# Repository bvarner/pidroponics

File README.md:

# pidroponics
RaspberryPi Controlled Hydroponics!

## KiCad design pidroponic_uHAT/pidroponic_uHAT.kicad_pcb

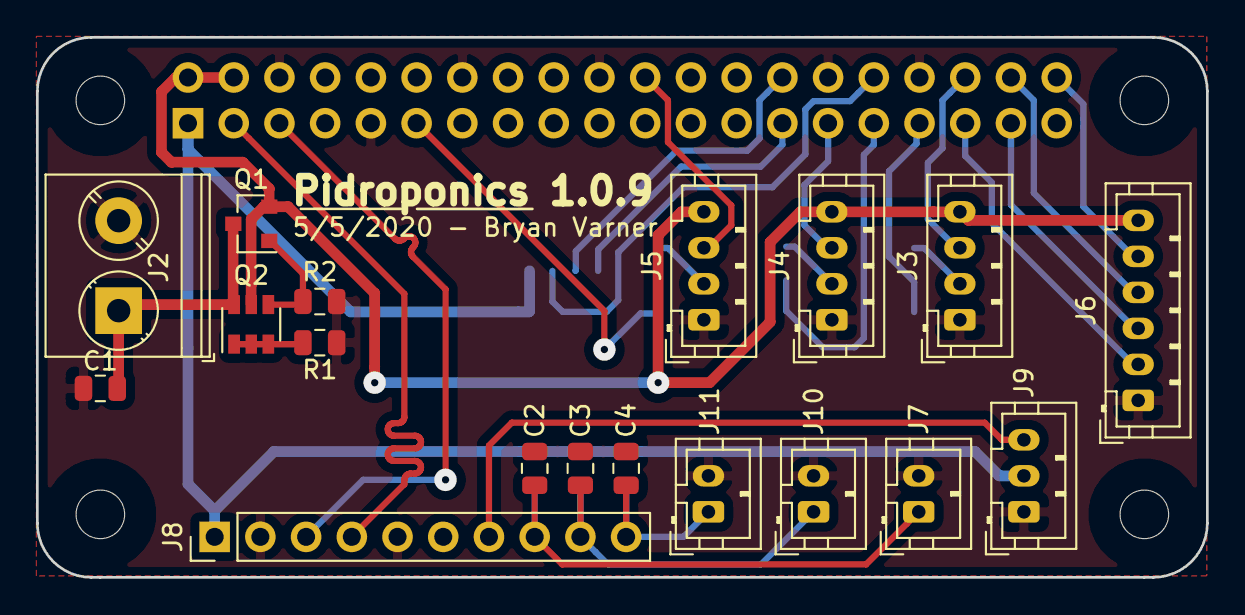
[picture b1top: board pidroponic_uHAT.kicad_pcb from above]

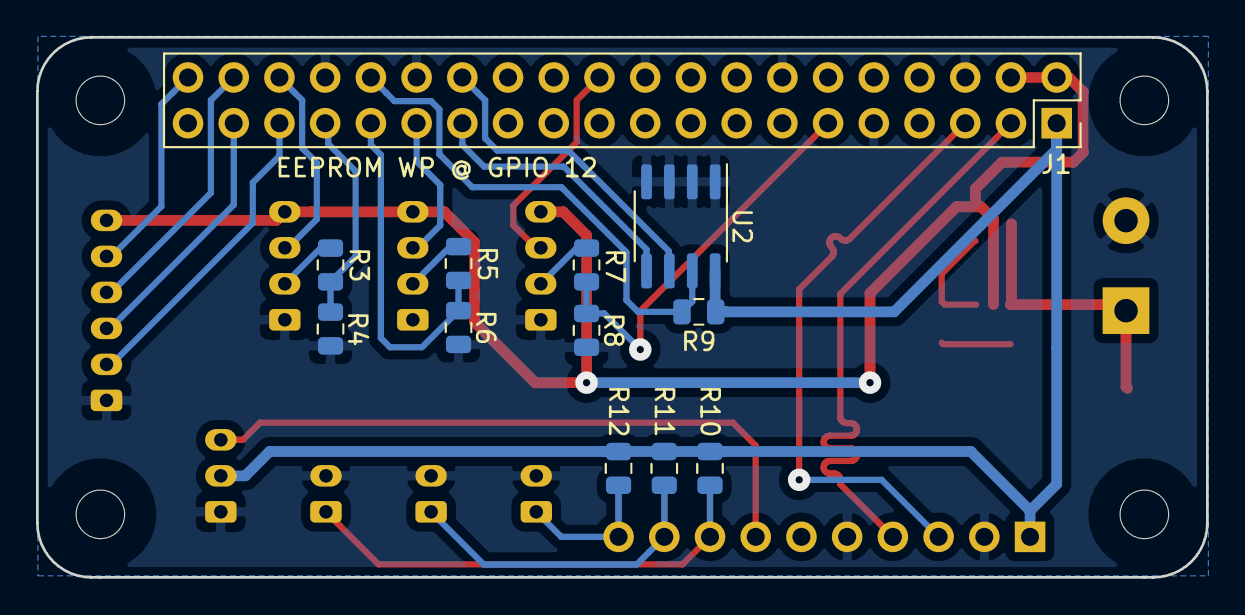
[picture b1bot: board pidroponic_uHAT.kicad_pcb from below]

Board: 2 copper layers, 65.0 x 30.0 mm, 34 parts (12 on the bottom side), 28 nets.

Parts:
C1, C2, C3, C4: 10uf; C_0805_2012Metric
H1, H2, H3, H4: MountingHole; MountingHole_2.7mm_M2.5_uHAT_RPi
J1: GPIO_CONNECTOR; PinSocket_2x20_P2.54mm_Vertical_Centered_Anchor
J2: 1935161; TerminalBlock_Phoenix_PT-1,5-2-5.0-H_1x02_P5.00mm_Horizontal
J3: Prox 0; JST_PH_B4B-PH-K_1x04_P2.00mm_Vertical
J4: Prox 1; JST_PH_B4B-PH-K_1x04_P2.00mm_Vertical
J5: Prox 2; JST_PH_B4B-PH-K_1x04_P2.00mm_Vertical
J6: 4 Chan Relay; JST_PH_B6B-PH-K_1x06_P2.00mm_Vertical
J7: Therm 0; JST_PH_B2B-PH-K_1x02_P2.00mm_Vertical
J8: TI ADS1115 Breakout Board; PinHeader_1x10_P2.54mm_Vertical
J9: Analog PH; JST_PH_B3B-PH-K_1x03_P2.00mm_Vertical
J10: Therm 1; JST_PH_B2B-PH-K_1x02_P2.00mm_Vertical
J11: Therm 2; JST_PH_B2B-PH-K_1x02_P2.00mm_Vertical
Q1: DMG2305UX-13; SOT-23
Q2: DMMT5401; SOT-23-6
R1, R9: 10K; R_0805_2012Metric
R2: 47K; R_0805_2012Metric
R3, R5, R7: 3k; R_0805_2012Metric
R4, R6, R8: 3.9k; R_0805_2012Metric
R10, R11, R12: 4.7k; R_0805_2012Metric
U2: CAT24C32; SOIC-8_3.9x4.9mm_P1.27mm

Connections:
+3V3: J1.1, J8.1, J9.2, R9.1, R10.1, R11.1, R12.1, U2.8
+5V: J1.2, J1.4, J3.4, J4.4, J5.4, J6.6, Q1.2, Q2.5
/A0: J8.7, J9.3
/A1: C2.1, J7.1, J8.8, R10.2
/A2: C3.1, J8.9, J10.1, R11.2
/A3: C4.1, J8.10, J11.1, R12.2
/ECHO_0: J3.2, R3.1
/ECHO_1: J4.2, R5.1
/ECHO_2: J5.2, R7.1
/EXT5V: C1.1, J2.1, Q1.3, Q2.6
/GPIO2_SDA1: J1.3, J8.4
/GPIO3_SCL1: J1.5, J8.3
/GPIO5: J1.29, J4.3
/GPIO6: J1.31, R5.2, R6.1
/GPIO12: J1.32, R9.2, U2.7
/GPIO13: J1.33, R3.2, R4.1
/GPIO16: J1.36, J3.3
/GPIO17: J1.11, R7.2, R8.1
/GPIO19: J1.35, J6.2
/GPIO20: J1.38, J6.4
/GPIO21: J1.40, J6.5
/GPIO25: J1.22, J5.3
/GPIO26: J1.37, J6.3
/ID_SC: J1.28, U2.6
/ID_SD: J1.27, U2.5
GND: C1.2, C2.2, C3.2, C4.2, J1.6, J1.9, J1.14, J1.20, J1.30, J1.34, J2.2, J3.1, J4.1, J5.1, J6.1, J7.2, J8.2, J8.5, J9.1, J10.2, J11.2, R1.2, R2.2, R4.2, R6.2, R8.2, U2.1, U2.2, U2.3, U2.4
unnamed: Q1.1, Q2.4, R2.1
unnamed: Q2.1, Q2.2, Q2.3, R1.1

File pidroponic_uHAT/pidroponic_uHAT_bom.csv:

Reference, Quantity, Value, Footprint, Datasheet, Description, Digi-Key_PN, Category, DK_Datasheet_Link, DK_Detail_Page, Family, MPN, Manufacturer, Status
C1 C2 ,2,"10uf","Capacitor_SMD:C_0805_2012Metric","~","CAP CER 10UF 16V X5R 0805","445-7644-1-ND","","","","","","",""
H1 H2 H3 H4 ,4,"MountingHole","lib:MountingHole_2.7mm_M2.5_uHAT_RPi","~"
J1 ,1,"GPIO_CONNECTOR","lib:PinSocket_2x20_P2.54mm_Vertical_Centered_Anchor","~"
J11 J10 J9 J7 ,4,"S2B-PH-K-S_LF__SN_","Connector_JST:JST_PH_B2B-PH-K_1x02_P2.00mm_Vertical","http://www.jst-mfg.com/product/pdf/eng/ePH.pdf","CONN HEADER R/A 2POS 2MM","455-1719-ND","Connectors, Interconnects","http://www.jst-mfg.com/product/pdf/eng/ePH.pdf","/product-detail/en/jst-sales-america-inc/S2B-PH-K-S(LF)(SN)/455-1719-ND/926626","Rectangular Connectors - Headers, Male Pins","S2B-PH-K-S(LF)(SN)","JST Sales America Inc.","Active"
J2 ,1,"1935161","digikey-footprints:Terminal_Block_D1.3mm_P5mm","https://media.digikey.com/pdf/Data%20Sheets/Phoenix%20Contac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","TERM BLK 2POS SIDE ENTRY 5MM PCB","277-1667-ND","Connectors, Interconnects","https://media.digikey.com/pdf/Data%20Sheets/Phoenix%20Contac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","/product-detail/en/phoenix-contact/1935161/277-1667-ND/568614","Terminal Blocks - Wire to Board","1935161","Phoenix Contact","Active"
J3 J4 J5 ,3,"B4B-PH-K-S_LF__SN_","Connector_JST:JST_PH_B4B-PH-K_1x04_P2.00mm_Vertical","http://www.jst-mfg.com/product/pdf/eng/ePH.pdf","CONN HEADER VERT 4POS 2MM","455-1706-ND","Connectors, Interconnects","http://www.jst-mfg.com/product/pdf/eng/ePH.pdf","/product-detail/en/jst-sales-america-inc/B4B-PH-K-S(LF)(SN)/455-1706-ND/926613","Rectangular Connectors - Headers, Male Pins","B4B-PH-K-S(LF)(SN)","JST Sales America Inc.","Active"
J6 ,1,"B6B-PH-K-S_LF__SN_","Connector_JST:JST_PH_B6B-PH-K_1x06_P2.00mm_Vertical","http://www.jst-mfg.com/product/pdf/eng/ePH.pdf","CONN HEADER VERT 6POS 2MM","455-1708-ND","Connectors, Interconnects","http://www.jst-mfg.com/product/pdf/eng/ePH.pdf","/product-detail/en/jst-sales-america-inc/B4B-PH-K-S(LF)(SN)/455-1706-ND/926613","Rectangular Connectors - Headers, Male Pins","B6B-PH-K-S(LF)(SN)","JST Sales America Inc.","Active"
J8 ,1,"TI ADS1115 Breakout","Connector_PinHeader_2.54mm:PinHeader_1x10_P2.54mm_Vertical","~"
Q1 ,1,"DMG2305UX-13","Package_TO_SOT_SMD:SOT-23","https://www.diodes.com/assets/Datasheets/DMG2305UX.pdf","MOSFET P-CH 20V 4.2A SOT23","DMG2305UX-13DICT-ND","Discrete Semiconductor Products","https://www.diodes.com/assets/Datasheets/DMG2305UX.pdf","/product-detail/en/diodes-incorporated/DMG2305UX-13/DMG2305UX-13DICT-ND/4251589","Transistors - FETs, MOSFETs - Single","DMG2305UX-13","Diodes Incorporated","Active"
Q2 ,1,"DMMT5401","Package_TO_SOT_SMD:SOT-23-6","","TRANS 2PNP 150V 0.2A SOT26","DMMT5401-FDICT-ND","","","","","","",""
R1 R9 ,2,"10K","Resistor_SMD:R_0805_2012Metric","~","RES 10K OHM 0.5% 1/8W 0805","RNCF0805DTE10K0CT-ND","","","","","","",""
R2 ,1,"47K","Resistor_SMD:R_0805_2012Metric","~","RES 47K OHM 0.5% 1/8W 0805","RNCF0805DTE47K0CT-ND","","","","","","",""
R3 R5 R7 ,3,"3k","Resistor_SMD:R_0805_2012Metric","~","RES 3K OHM 0.5% 1/8W 0805","RNCF0805DTE3K00CT-ND","","","","","","",""
R4 R6 R8 ,3,"3.9k","Resistor_SMD:R_0805_2012Metric","~","RES 3.9K OHM 0.5% 1/8W 0805","RNCF0805DTE3K90CT-ND","","","","","","",""
U1 ,1,"LM7805_TO220","Package_TO_SOT_THT:TO-220-3_Vertical","http://www.fairchildsemi.com/ds/LM/LM7805.pdf","IC REG LINEAR 5V 1A TO220-3","296-47192-ND","","","","","","",""
U2 ,1,"CAT24C32","Package_SO:SOIC-8_3.9x4.9mm_P1.27mm","https://www.onsemi.com/pub/Collateral/CAT24C128-D.PDF","IC EEPROM 32K I2C 1MHZ 8SOIC","CAT24C32WI-GT3CT-ND","","","","","","",""

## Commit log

2020-04-14 Added the initial pass at making this thing.
2020-04-14 Initial HTML stub.
2020-04-14 Adding go dep bits.
2020-04-14 Fixing some things for go 1.12.x
2020-04-14 Make it use ns conversions.
2020-04-14 Adding some more debug bits.
2020-04-14 Removing the second sensor from the code to debug...
2020-04-14 Cleaning up some things to see if we can get better numbers.
2020-04-14 When you brain-fart so hard... git push
2020-04-14 Lots of combinations.
2020-04-14 I'm getting some consistency in numbers, but the numbers look off.
2020-04-14 edge triggers for both edges are not reliable.
2020-04-14 Gutting this thing. If I can't get accurate measurements with periph.io, I'll have to drop back to driver dev land.
2020-04-14 Ns to S.
2020-04-24 * Added the SSE broker. * Added Emitter Support. * Removed the user-land really terrible code for interacting with the transceivers.
2020-04-24 Adding the uHAT hardware.
2020-04-24 Updated the deps
2020-04-24 Fixed allocate and assign to just assign.
2020-04-24 Convert to idiomatic method for returning error.
2020-04-24 Extra logging.
2020-04-24 * enumerating with path.join
2020-04-24 * Read device paths a bit better and take more appropriate actions.
2020-04-24 Be a bit more verbose about the dev name path.
2020-04-24 feel like i've been had. path.join just joins and checks for the prescence of a 'slash'
2020-04-24 echo the devicename buffer.
2020-04-25 Trying to get the device name to read properly.
2020-04-25 ioutils.readfile is returning the line-feed at the end of the device name contents.
2020-04-25 Adding very rough, initial HTTP endpoints.)
2020-04-25 I think I forgot the zero index offset.
2020-04-25 Nope it was an inverted sanity check.
2020-04-25 Try this initializer
2020-04-25 Subtree.... ugh.
2020-04-25 Let us GET and PUT.
2020-04-25 Eh, I hate early returns
2020-04-25 A bit of error handling cleanup
2020-04-25 I think we'll try this to see if it's cleaner.
2020-04-25 Forgot to implement the emitter interface.
2020-04-25 I forgot it was relay state being emitted.
2020-04-25 Yikes. '
2020-04-25 Why is this not working
2020-04-25 Why is this failing.
2020-04-25 I wonder....
2020-04-25 Found it. Some obscure pointer settings.
2020-04-25 Initial SRF04 support?
2020-04-26 A small commit for SRF04 support.
2020-04-26 working on it.
2020-04-26 The device returns a timeout from 'cat' but the goland read tools just hit EOF.
2020-04-26 Zero bytes signifies and unexpected EOF
2020-04-26 Debugging...
2020-04-26 Something isn't right here, but I'm not sure what.
2020-04-26 Looks like ReadFile is a bit... aggressive.
2020-04-26 Let's just keep doing this for a bit.
2020-04-26 I think I have a stream timing out.
2020-04-26 Pretty sure it's something to do with file modes.
2020-04-26 This should let us know if it's a timeout.
2020-04-27 Try opening it like a socket?
2020-04-27 Let's see what readfull does.
2020-04-27 So it's a ReadFull Issue. Yay.
2020-04-27 Oh, let's see what our buffer is.
2020-04-27 Hahahaha I bet it's ASCII or character codes.
2020-04-27 Let's remove the initial 'read' and see what happens.
2020-04-27 I probably should use readfull. I'm going to open / close a lot.
2020-04-27 Update to set read deadline.
2020-04-27 This should be a mess.
2020-04-27 Let's try it as a char device.
2020-04-27 Bigger buffer...
2020-04-27 Oh boy.
2020-04-27 Posted on stackoverflow, falling back to os.exec
2020-04-27 trying to debug my init sequence. which turned rather messy in all this
2020-04-27 os.exec.Output returns the \n
2020-04-27 Implemented some wretched nasty read/skip logic.
2020-04-27 Wow. I missed a compile error
2020-04-27 Looks like read/skip works.
2020-04-27 small tweak for comments.
2020-04-29 updates over the last few evenings.
2020-04-29 I bet this works better.
2020-04-29 Negative. I am a meat popscicle.
2020-04-29 Sometimes two reads just aren't enought.
2020-04-29 Oh, slow down there parder.
2020-04-29 Let's do it 3 times a second.
2020-04-29 6 reads per second over the file io method.
2020-04-29 Dump this out to see what's blowing up.
2020-04-29 Dude. What was I thinking.
2020-04-29 I hate traditional I/O
2020-04-29 Try rewinding.
2020-04-29 I keep trying to make this faster.
2020-04-29 debug...
2020-04-29 tighten up
2020-04-29 remove paranoid seek
2020-04-29 Add a bunch'o stuff '
2020-04-29 see if this can happen
2020-04-29 Wow. Transponders are finally stable.
2020-04-29 Ok, SRF04's are working.
2020-04-30 Initial addition of ADS1115 support via IIO triggered buffers.... using the sysfs
2020-04-30 forgot to update this part.
2020-04-30 use a slash... because apparently I cant add the rune unless I strcat
2020-04-30 I knew I forgot something.
2020-04-30 Let's see how we do here.
2020-05-05 Update to the uHAT, given learning new things.
    * Removed the 5v linear regulator. Relays draw too much current for this to be safe. Off-board switching DC-DC buck converters are inexpensive up to 3A. Recommend using an LM2596 board.
    * ADC pins configured for 3 thermistors (4.7k pullup through thermistor + filter cap) + one direct ADC feed for connecting a 3.3v analog PH Sensor
    * Unified board design specs to make the 'fab' one the same as the 'homeproto'. We'll try traces this big with home proto and see where that gets us. In that vein, removed all but four vias.
    General notes about this version:
    * Soldering both sides of the header pins makes it possible to use those pads as vias, greatly
2020-05-08 * Refactoring device detection. * Cleaning up init. * MOving toward getting the NTC and the PH Detector setup.
2020-05-08 Refactored for consistency and clarity.
2020-05-11 Adding initial support for ntc-thermistors...
2020-05-11 Implemented initial NTC support.
2020-05-11 yeah, these put out temperatures.
2020-05-11 * decoupled broadcast from poll. * Ph probe userspace support. * mutexes protecting rings.
2020-05-11 Update the names.
2020-05-11 Independent broadcast tickers
2020-05-11 Emit each device each second.
2020-05-11 Give an obviously bs number instead of NAN
2020-05-11 That works better.
2020-05-11 Should expose the rest APIs.
2020-05-11 Debugging the control loop...
2020-05-11 This may actually control some things.
2020-05-11 Allow for manual to override the schedule.
2020-05-28 Pidroponics 1.0.9 PCB & Gerbers.
2020-05-29 Decimal shift...
2020-05-29 Documentation
2020-06-03 Updating to try and latch changes for a few seconds.
2020-06-05 Updating to add prometheus metrics
2020-06-05 Adding Metrics for all sensors.
2020-06-05 Adding Metrics for relays and cleaning up imports
2020-06-08 It's returning 0 for some reason.
2020-06-08 Update the tick to send distance metrics.
2020-06-16 * Updated to emit gauge vectors. * SamplePoint introduced as a very terrible enum.
2020-06-16 Apparently subsystem can't be nil
2020-06-16 This actually made a lot more sense.
2020-06-17 Just realized this was cribbed and not updated. :-)
2020-06-22 Millivolts. Yo.

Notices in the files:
pidroponic_uHAT/pidroponic_uHAT.kicad_pcb:
This PCB design is licensed under MIT Open Source License.
